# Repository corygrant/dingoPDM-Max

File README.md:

## dingoPDM-Max
dingoPDM-Max is an Infineon Profet based Power Distribution Module. 

# [**Documentation**](https://corygrant.github.io/dingoPDM/)

# [**Store**](https://dingo-electronics.square.site/product/dingopdm-max/9)

## Disclaimer
Please note that this product has been designed by a hobbyist, not a professional. It is intended for off-road and testing use only. Users should operate the product at their own discretion and risk. The designer explicitly disclaims any responsibility for damage or injury that may result from the use of this product.

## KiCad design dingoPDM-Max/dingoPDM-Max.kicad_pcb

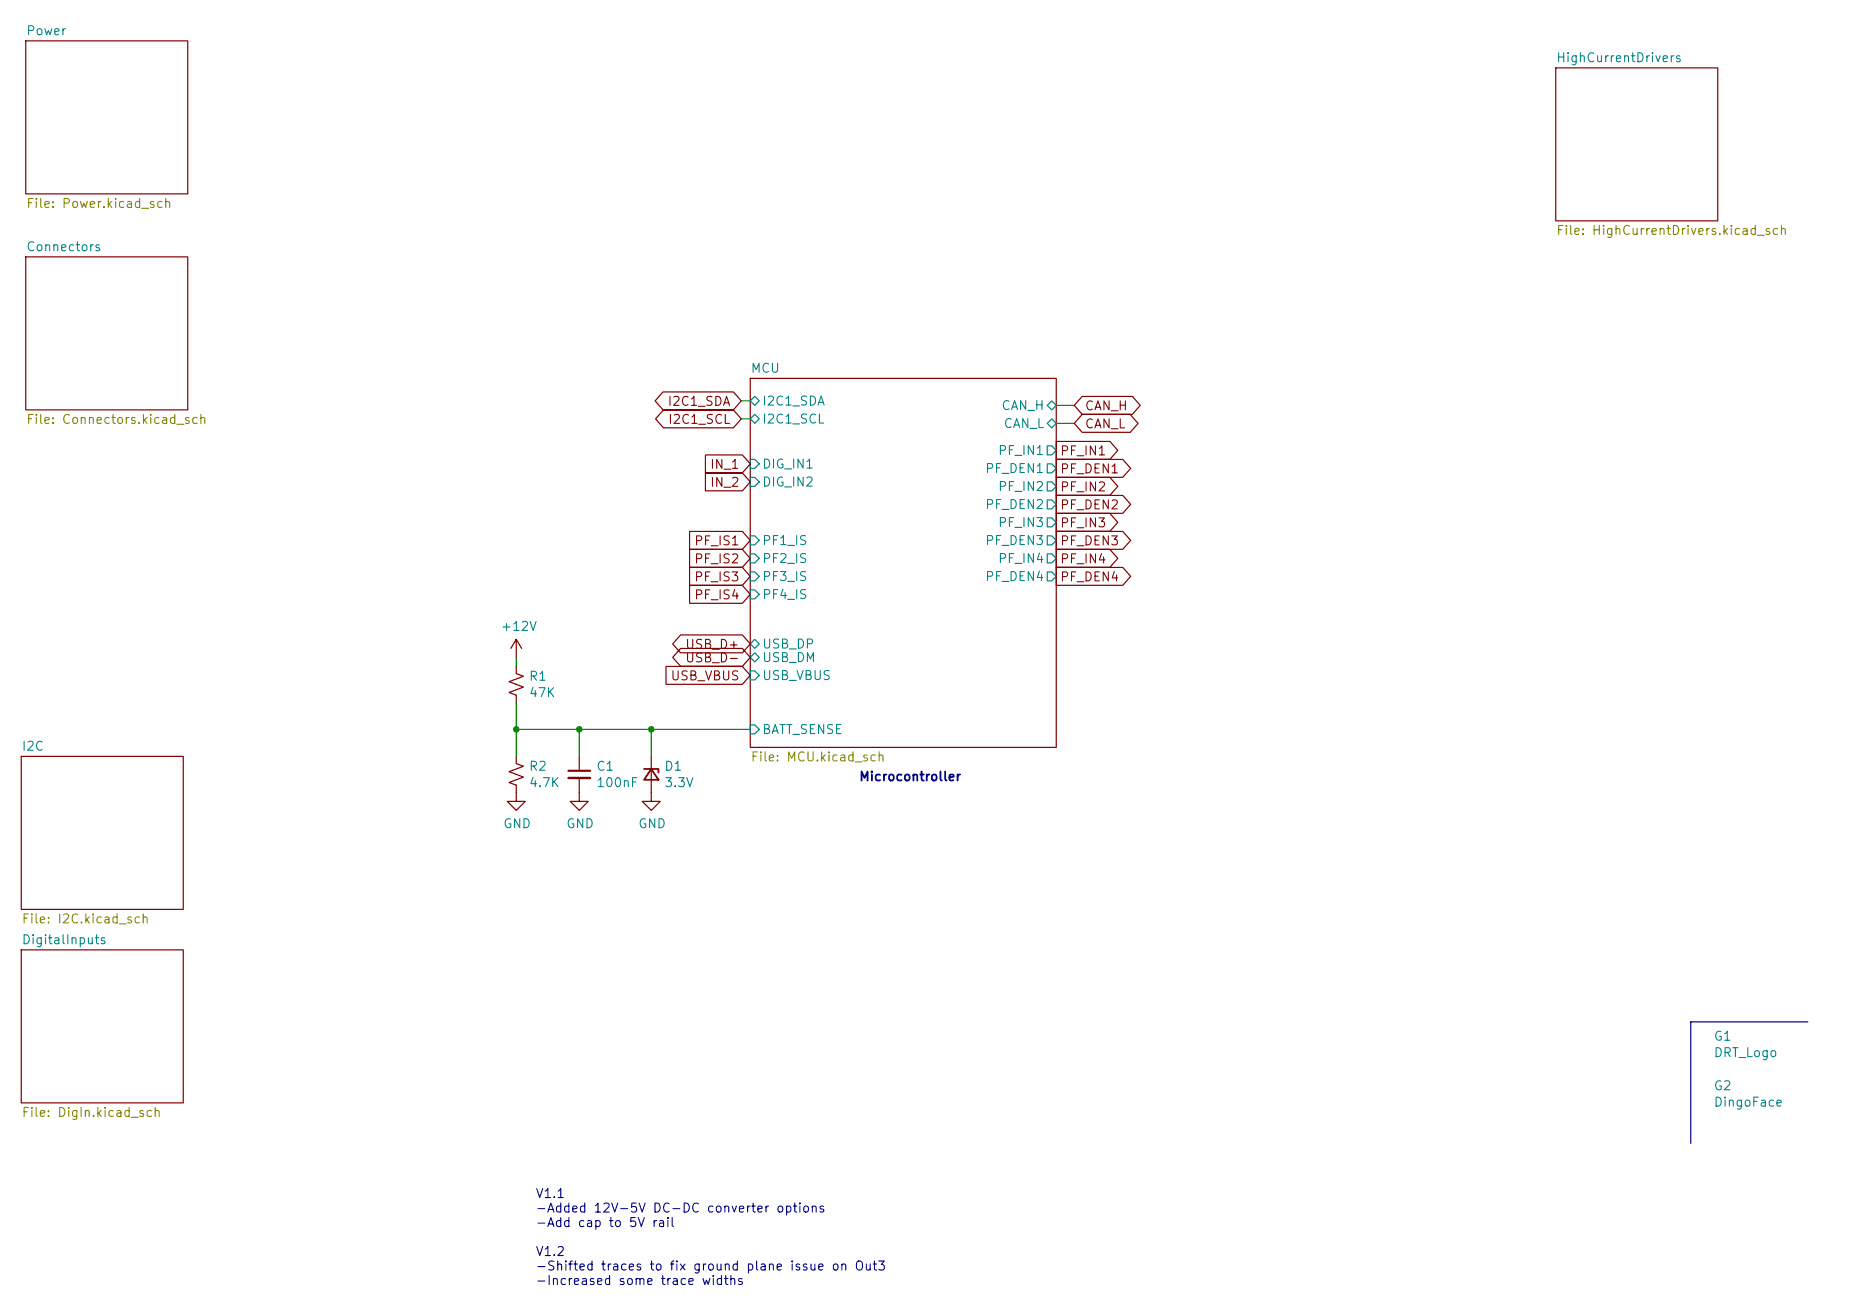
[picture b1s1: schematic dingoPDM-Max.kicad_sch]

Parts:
C1: 100nF; C_0805_2012Metric; Digi-Key_PN 478-1395-1-ND
D1: 3.3V; D_SOD-323_HandSoldering; Digi-Key_PN 1727-5150-1-ND
G1: DRT_Logo; DRTLogo
G2: DingoFace; DingoFaceNoFill
R1: 47K; R_0805_2012Metric; Digi-Key_PN 311-47.0KCRCT-ND
R2: 4.7K; R_0805_2012Metric; Digi-Key_PN 311-4.70KCRCT-ND

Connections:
+12V: R1.1; also elsewhere on the board
/MCU/BATT_SENSE: C1.1, D1.1 (K), R1.2, R2.1; also elsewhere on the board
GND: C1.2, D1.2 (A), R2.2; also elsewhere on the board

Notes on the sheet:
Microcontroller
V1.1 -Added 12V-5V DC-DC converter options -Add cap to 5V rail V1.2 -Shifted traces to fix ground plane issue on Out3 -Increased some trace widths

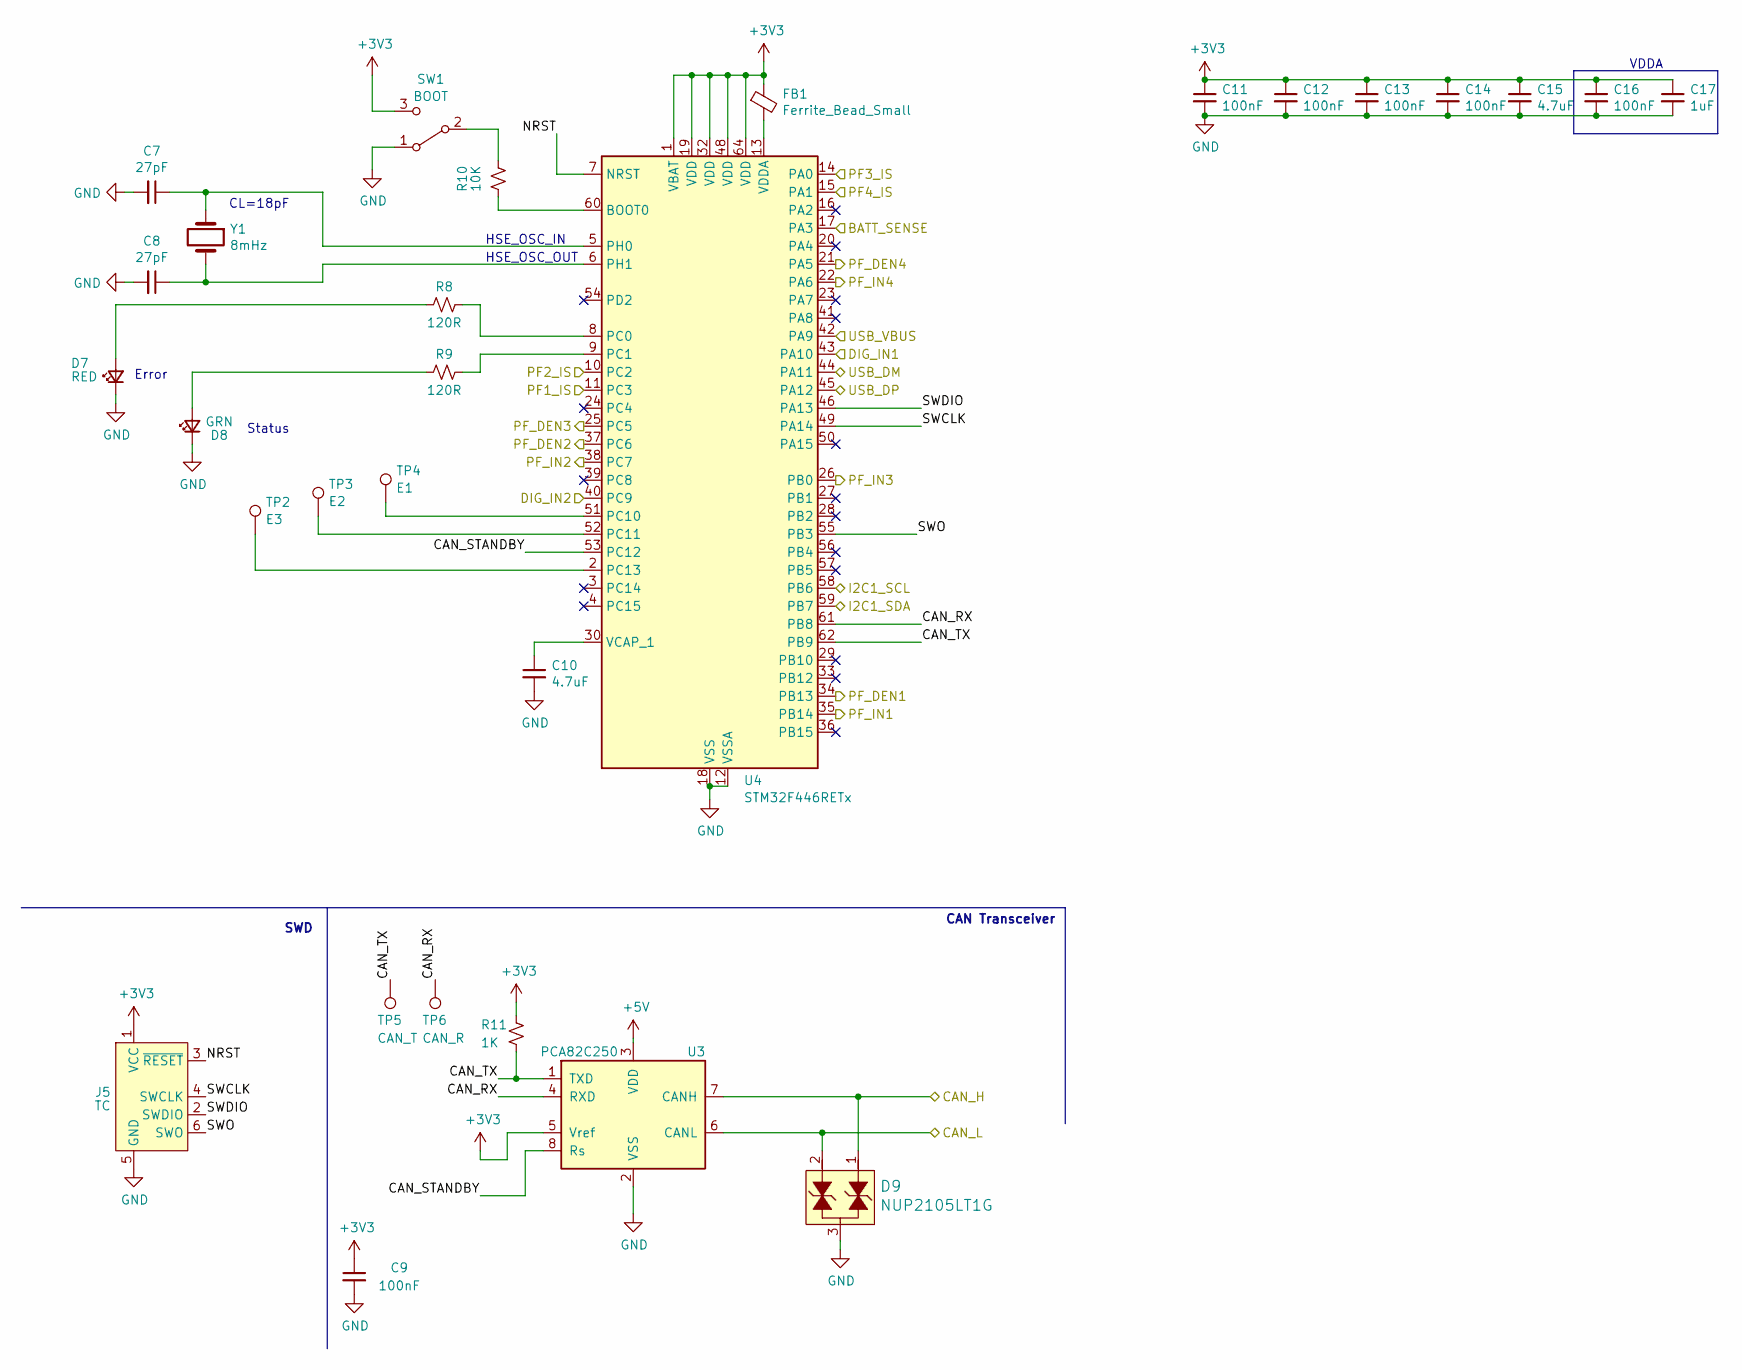
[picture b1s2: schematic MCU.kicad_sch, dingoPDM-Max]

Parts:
C7, C8: 27pF; C_0805_2012Metric; Digi-Key_PN 478-10518-1-ND
C9, C11, C12, C13, C14, C16: 100nF; C_0805_2012Metric; Digi-Key_PN 478-1395-1-ND
C10, C15: 4.7uF; C_0805_2012Metric; Digi-Key_PN 1276-2873-1-ND
C17: 1uF; C_0805_2012Metric; Digi-Key_PN 311-1365-1-ND
D7: RED; LED_0805_2012Metric; Digi-Key_PN 475-1278-1-ND
D8: GRN; LED_0805_2012Metric; Digi-Key_PN 475-1410-1-ND
D9: NUP2105LT1G; SOT-23-3; Digi-Key_PN NUP2105LT1GOSCT-ND
FB1: Ferrite_Bead_Small; R_0805_2012Metric; Digi-Key_PN 490-1054-1-ND
J5: TC; Tag-Connect_TC2030-IDC-NL_2x03_P1.27mm_Vertical
R8, R9: 120R; R_0805_2012Metric; Digi-Key_PN 311-120CRCT-ND
R10: 10K; R_0805_2012Metric; Digi-Key_PN 311-10.0KCRDKR-ND
R11: 1K; R_0805_2012Metric; Digi-Key_PN 311-1.0KARCT-ND
SW1: BOOT; CJS-1200TB; Digi-Key_PN 563-CJS-1200TB1CT-ND
TP2: E3; TestPoint_Keystone_5000-5004_Miniature
TP3: E2; TestPoint_Keystone_5000-5004_Miniature
TP4: E1; TestPoint_Keystone_5000-5004_Miniature
TP5: CAN_T; TestPoint_Keystone_5000-5004_Miniature
TP6: CAN_R; TestPoint_Keystone_5000-5004_Miniature
U3: PCA82C250; SOIC-8_3.9x4.9mm_P1.27mm; Digi-Key_PN 568-10316-1-ND
U4: STM32F446RETx; LQFP-64_10x10mm_P0.5mm; Digi-Key_PN 497-15376-ND
Y1: 8mHz; Crystal_SMD_5032-2Pin_5.0x3.2mm_HandSoldering; Digi-Key_PN 535-10630-1-ND

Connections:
+3V3: C9.1, C11.1, C12.1, C13.1, C14.1, C15.1, C16.1, C17.1, FB1.1, J5.1 (VCC), R11.2, SW1.3 (C), U3.5 (Vref), U4.1 (VBAT), U4.19 (VDD), U4.32 (VDD), U4.48 (VDD), U4.64 (VDD); also elsewhere on the board
+5V: U3.3 (VDD); also elsewhere on the board
/MCU/BATT_SENSE: U4.17 (PA3); also elsewhere on the board
/MCU/CAN_RX: TP6.1, U3.4 (RXD), U4.61 (PB8)
/MCU/CAN_STANDBY: U3.8 (Rs), U4.53 (PC12)
/MCU/CAN_TX: R11.1, TP5.1, U3.1 (TXD), U4.62 (PB9)
/MCU/NRST: J5.3 (~RESET), U4.7 (NRST)
/MCU/SWCLK: J5.4 (SWCLK), U4.49 (PA14)
/MCU/SWDIO: J5.2 (SWDIO), U4.46 (PA13)
/MCU/SWO: J5.6 (SWO), U4.55 (PB3)
CAN_H: D9.1, U3.7 (CANH); also elsewhere on the board
CAN_L: D9.2, U3.6 (CANL); also elsewhere on the board
GND: C7.2, C8.2, C9.2, C10.2, C11.2, C12.2, C13.2, C14.2, C15.2, C16.2, C17.2, D7.1 (K), D8.1 (K), D9.3, J5.5 (GND), SW1.1 (A), U3.2 (VSS), U4.12 (VSSA), U4.18 (VSS), U4.31 (VSS), U4.47 (VSS), U4.63 (VSS); also elsewhere on the board
I2C1_SCL: U4.58 (PB6); also elsewhere on the board
I2C1_SDA: U4.59 (PB7); also elsewhere on the board
IN_1: U4.43 (PA10); also elsewhere on the board
IN_2: U4.40 (PC9); also elsewhere on the board
unnamed: D7.2 (A), R8.2
unnamed: D8.2 (A), R9.2
unnamed: R10.1, SW1.2 (B)
unnamed: R10.2, U4.60 (BOOT0)
unnamed: R8.1, U4.8 (PC0)
unnamed: R9.1, U4.9 (PC1)
unnamed: TP4.1, U4.51 (PC10)
unnamed: TP3.1, U4.52 (PC11)
unnamed: TP2.1, U4.2 (PC13)
unnamed: C7.1, U4.5 (PH0), Y1.1
unnamed: C8.1, U4.6 (PH1), Y1.2
unnamed: C10.1, U4.30 (VCAP_1)
unnamed: FB1.2, U4.13 (VDDA)
PF_DEN1: U4.34 (PB13); also elsewhere on the board
PF_DEN2: U4.37 (PC6); also elsewhere on the board
PF_DEN3: U4.25 (PC5); also elsewhere on the board
PF_DEN4: U4.21 (PA5); also elsewhere on the board
PF_IN1: U4.35 (PB14); also elsewhere on the board
PF_IN2: U4.38 (PC7); also elsewhere on the board
PF_IN3: U4.26 (PB0); also elsewhere on the board
PF_IN4: U4.22 (PA6); also elsewhere on the board
PF_IS1: U4.11 (PC3); also elsewhere on the board
PF_IS2: U4.10 (PC2); also elsewhere on the board
PF_IS3: U4.14 (PA0); also elsewhere on the board
PF_IS4: U4.15 (PA1); also elsewhere on the board
USB_D+: U4.45 (PA12); also elsewhere on the board
USB_D-: U4.44 (PA11); also elsewhere on the board
USB_VBUS: U4.42 (PA9); also elsewhere on the board

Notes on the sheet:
SWD
Error
CAN Transceiver
HSE_OSC_IN
CL=18pF
HSE_OSC_OUT
VDDA
Status

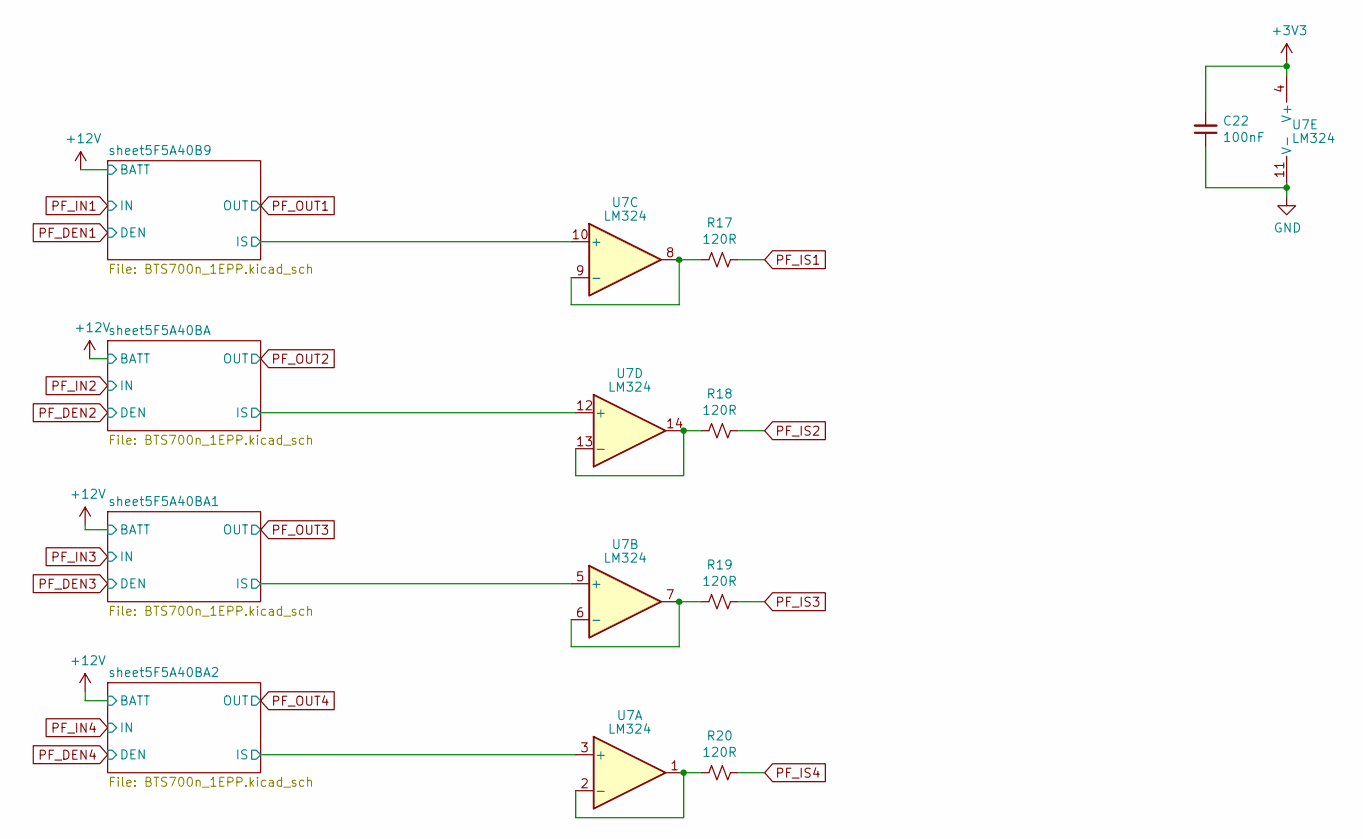
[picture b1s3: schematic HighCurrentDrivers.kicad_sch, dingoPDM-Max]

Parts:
C22: 100nF; C_0805_2012Metric; Digi-Key_PN 478-1395-1-ND
R17, R18, R19, R20: 120R; R_0805_2012Metric; Digi-Key_PN 311-120CRCT-ND
U7: LM324; TSSOP-14_4.4x5mm_P0.65mm; Digi-Key_PN 497-7330-1-ND

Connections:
+3V3: C22.2, U7.4 (V+); also elsewhere on the board
/HighCurrentDrivers/sheet5F5A40B9/IS: U7.10 (+); also elsewhere on the board
/HighCurrentDrivers/sheet5F5A40BA1/IS: U7.5 (+); also elsewhere on the board
/HighCurrentDrivers/sheet5F5A40BA2/IS: U7.3 (+); also elsewhere on the board
/HighCurrentDrivers/sheet5F5A40BA/IS: U7.12 (+); also elsewhere on the board
GND: C22.1, U7.11 (V-); also elsewhere on the board
unnamed: R20.2, U7.1, U7.2 (-)
unnamed: R19.2, U7.6 (-), U7.7
unnamed: R17.2, U7.8, U7.9 (-)
unnamed: R18.2, U7.13 (-), U7.14
PF_IS1: R17.1; also elsewhere on the board
PF_IS2: R18.1; also elsewhere on the board
PF_IS3: R19.1; also elsewhere on the board
PF_IS4: R20.1; also elsewhere on the board

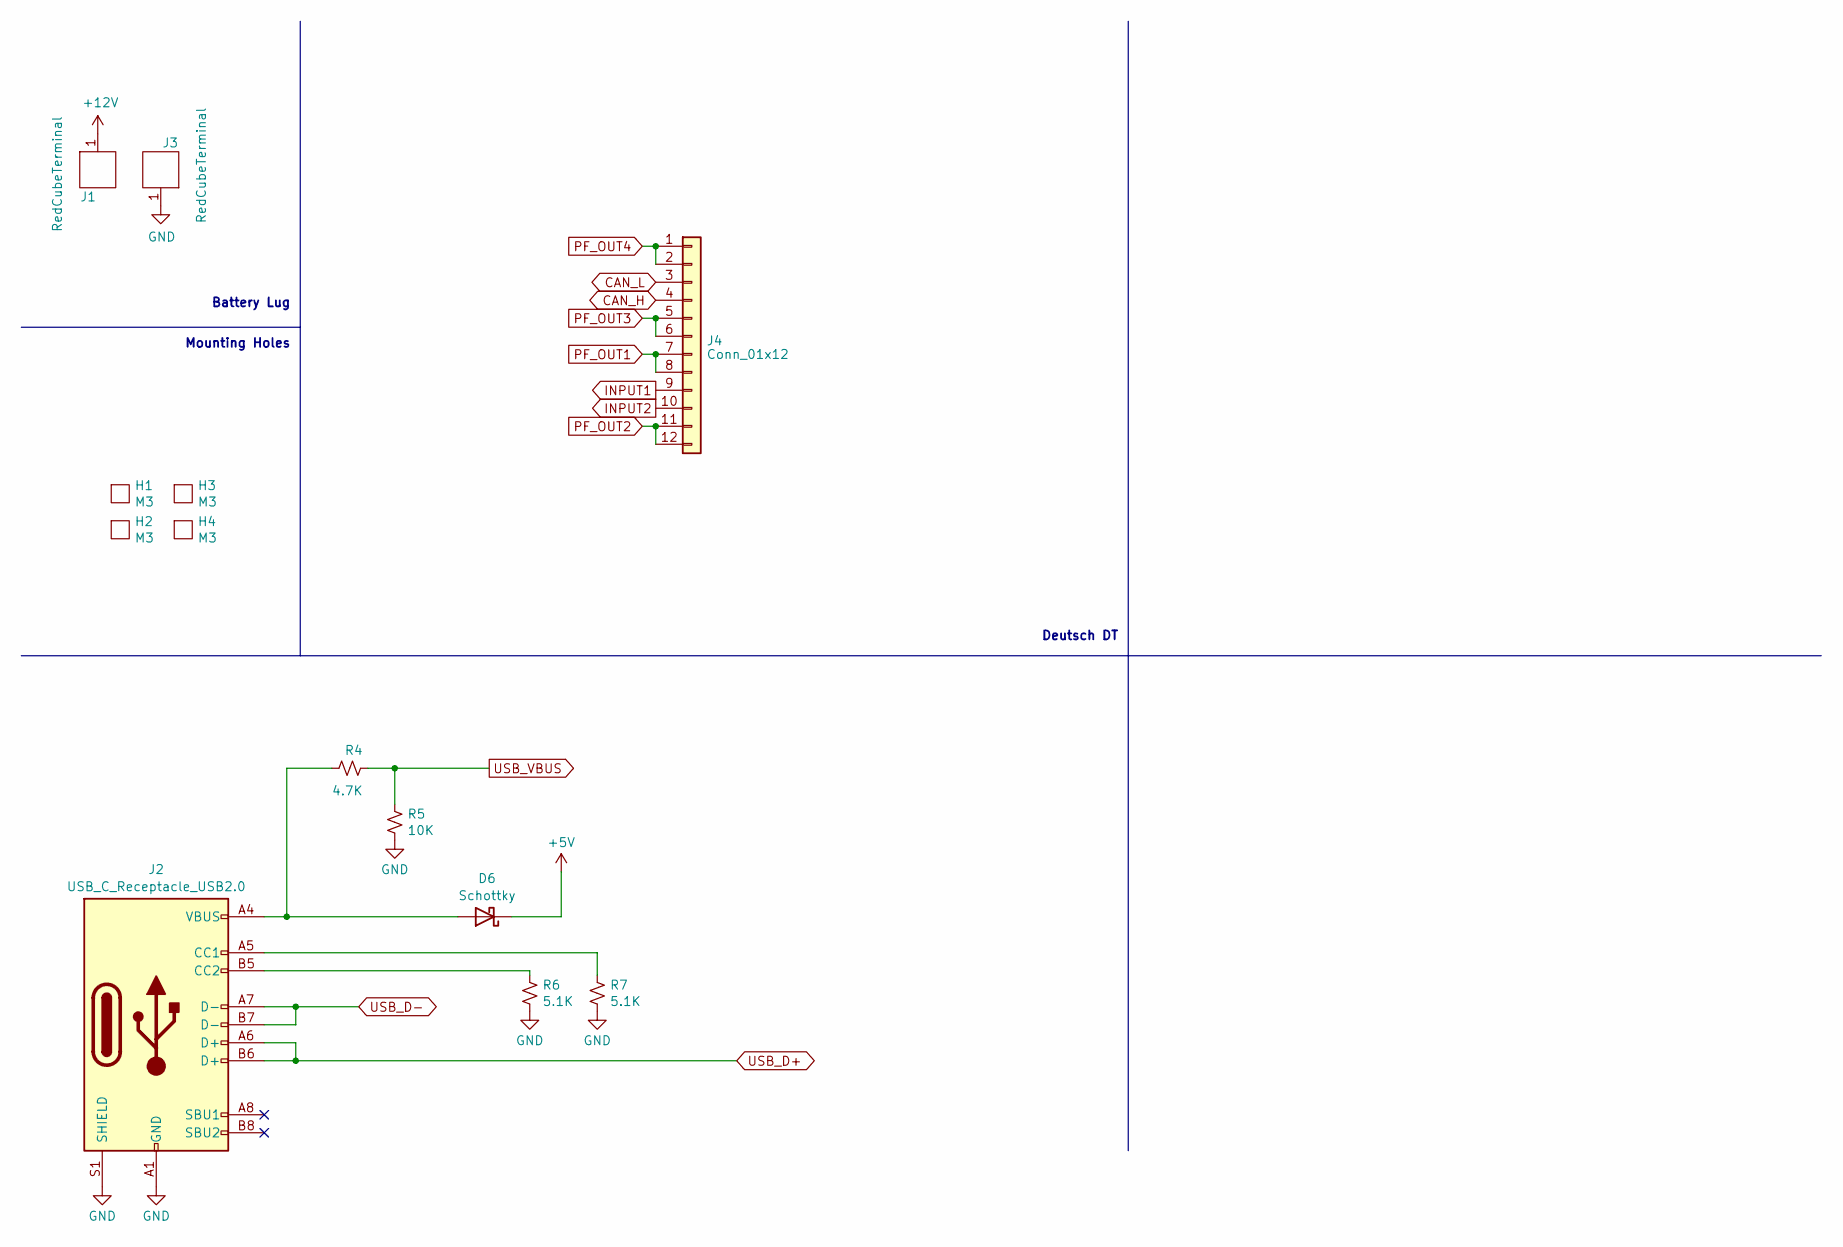
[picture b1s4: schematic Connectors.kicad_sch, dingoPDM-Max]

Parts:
D6: Schottky; D_SOD-123; Digi-Key_PN 1727-2394-1-ND
H1, H2, H3, H4: M3; MountingHole_3.2mm_M3_ISO7380_Pad
J1, J3: RedCubeTerminal; M6_Hole_8Pin_7461084; Digi-Key_PN 732-3203-ND
J2: USB_C_Receptacle_USB2.0; USB_C_Receptacle_GCT_USB4085; Digi-Key_PN 2073-USB4085-GF-ACT-ND
J4: Conn_01x12; DT15-12PA; LCSC C5341788
R4: 4.7K; R_0805_2012Metric; Digi-Key_PN 311-4.70KCRCT-ND
R5: 10K; R_0805_2012Metric; Digi-Key_PN 311-10.0KCRDKR-ND
R6, R7: 5.1K; R_0805_2012Metric; Digi-Key_PN 311-5.1KARCT-ND

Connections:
+5V: D6.1 (K); also elsewhere on the board
+12V: J1.1; also elsewhere on the board
CAN_H: J4.4; also elsewhere on the board
CAN_L: J4.3; also elsewhere on the board
GND: J2.A1 (GND), J2.A12 (GND), J2.B1 (GND), J2.B12 (GND), J2.S1 (SHIELD), J3.1, R5.2, R6.2, R7.2; also elsewhere on the board
INPUT1: J4.9; also elsewhere on the board
INPUT2: J4.10; also elsewhere on the board
unnamed: D6.2 (A), J2.A4 (VBUS), J2.A9 (VBUS), J2.B4 (VBUS), J2.B9 (VBUS), R4.1
unnamed: J2.A5 (CC1), R7.1
unnamed: J2.B5 (CC2), R6.1
PF_OUT1: J4.7, J4.8; also elsewhere on the board
PF_OUT2: J4.11, J4.12; also elsewhere on the board
PF_OUT3: J4.5, J4.6; also elsewhere on the board
PF_OUT4: J4.1, J4.2; also elsewhere on the board
USB_D+: J2.A6 (D+), J2.B6 (D+); also elsewhere on the board
USB_D-: J2.A7 (D-), J2.B7 (D-); also elsewhere on the board
USB_VBUS: R4.2, R5.1; also elsewhere on the board

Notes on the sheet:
Deutsch DT
Battery Lug
Mounting Holes

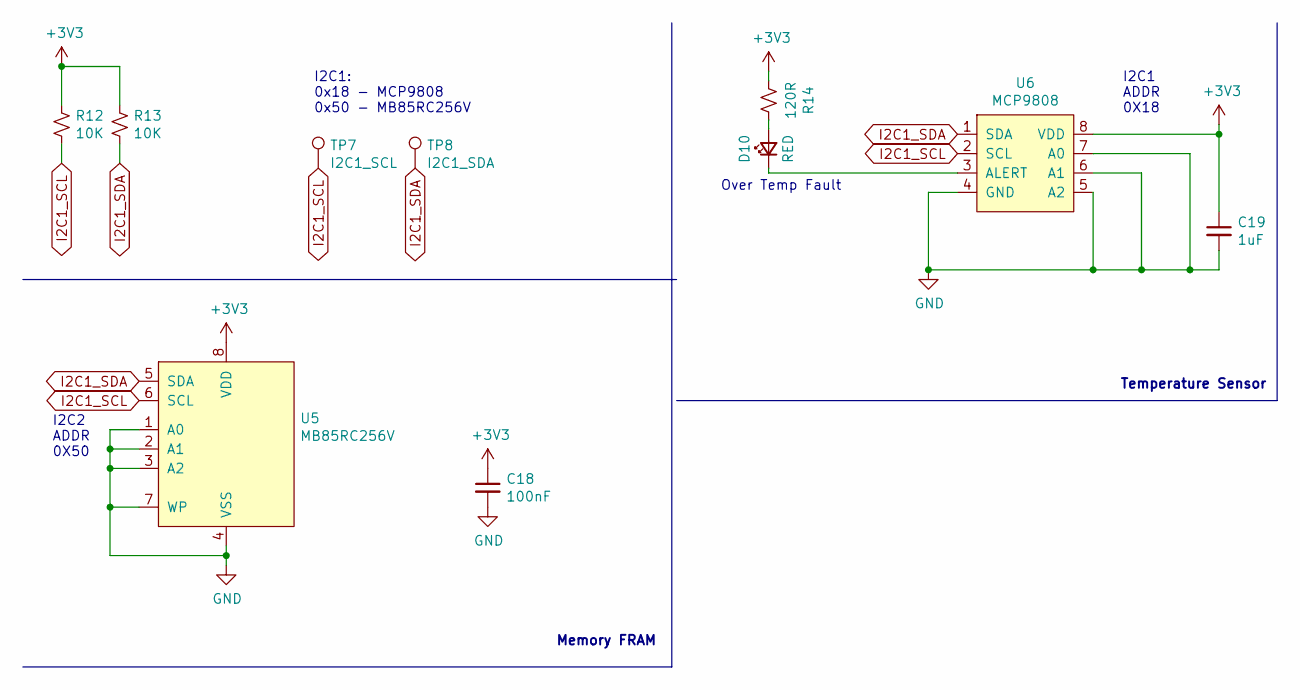
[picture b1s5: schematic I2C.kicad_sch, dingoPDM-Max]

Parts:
C18: 100nF; C_0805_2012Metric; Digi-Key_PN 478-1395-1-ND
C19: 1uF; C_0805_2012Metric; Digi-Key_PN 311-1365-1-ND
D10: RED; LED_0805_2012Metric; Digi-Key_PN 475-1278-1-ND
R12, R13: 10K; R_0805_2012Metric; Digi-Key_PN 311-10.0KCRDKR-ND
R14: 120R; R_0805_2012Metric; Digi-Key_PN 311-120CRCT-ND
TP7: I2C1_SCL; TestPoint_Keystone_5000-5004_Miniature
TP8: I2C1_SDA; TestPoint_Keystone_5000-5004_Miniature
U5: MB85RC256V; SOIC-8_3.9x4.9mm_P1.27mm; Digi-Key_PN 865-1261-1-ND
U6: MCP9808; MSOP-8_3x3mm_P0.65mm; Digi-Key_PN MCP9808T-E/MSCT-ND

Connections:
+3V3: C18.1, C19.1, R12.1, R13.1, R14.2, U5.8 (VDD), U6.8 (VDD); also elsewhere on the board
GND: C18.2, C19.2, U5.1 (A0), U5.2 (A1), U5.3 (A2), U5.4 (VSS), U5.7 (WP), U6.4 (GND), U6.5 (A2), U6.6 (A1), U6.7 (A0); also elsewhere on the board
I2C1_SCL: R12.2, TP7.1, U5.6 (SCL), U6.2 (SCL); also elsewhere on the board
I2C1_SDA: R13.2, TP8.1, U5.5 (SDA), U6.1 (SDA); also elsewhere on the board
unnamed: D10.2 (A), R14.1
unnamed: D10.1 (K), U6.3 (ALERT)

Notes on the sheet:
I2C1 ADDR 0X18
I2C2 ADDR 0X50
Over Temp Fault
Temperature Sensor
I2C1: 0x18 - MCP9808 0x50 - MB85RC256V
Memory FRAM

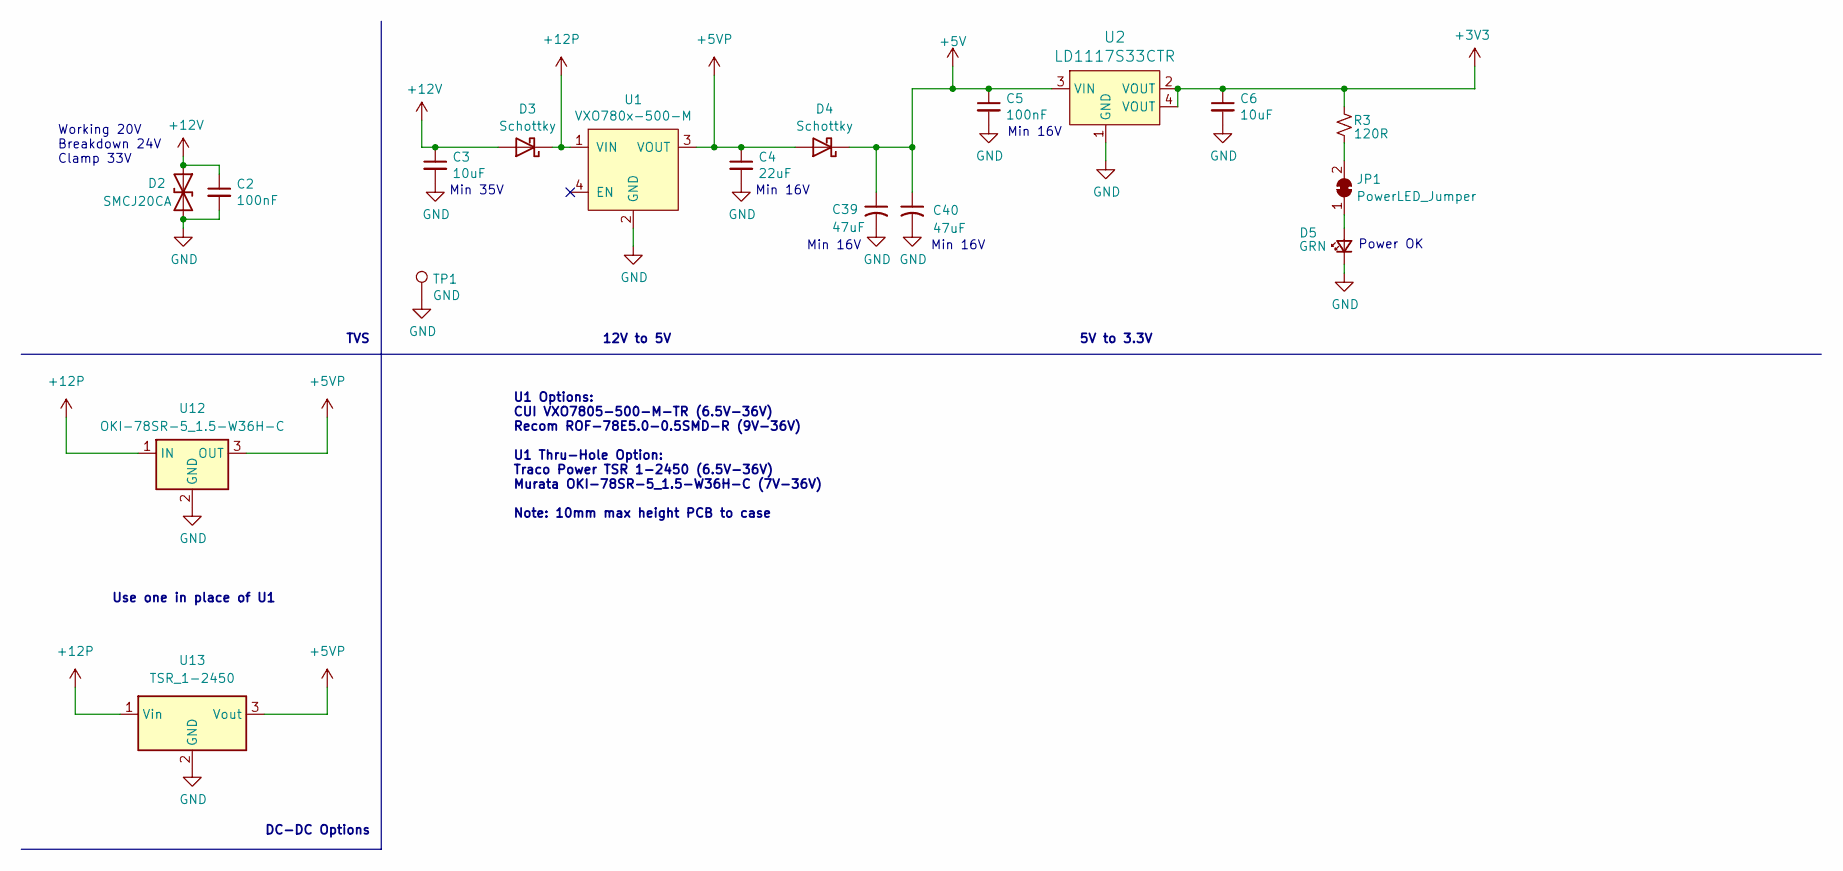
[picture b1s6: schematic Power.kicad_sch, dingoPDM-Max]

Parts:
C2, C5: 100nF; C_0805_2012Metric; Digi-Key_PN 478-1395-1-ND
C3, C6: 10uF; C_0805_2012Metric; Digi-Key_PN 445-11516-1-ND
C4: 22uF; C_0805_2012Metric; Digi-Key_PN 490-10749-1-ND
C39, C40: 47uF; C_2220_5750Metric; Digi-Key_PN 445-7935-1-ND
D2: SMCJ20CA; DO-214AB_TVS; Digi-Key_PN SMCJ20CABCT-ND
D3, D4: Schottky; D_SOD-123; Digi-Key_PN 1727-2394-1-ND
D5: GRN; LED_0805_2012Metric; Digi-Key_PN 475-1410-1-ND
JP1: PowerLED_Jumper; SolderJumper-2_P1.3mm_Bridged_RoundedPad1.0x1.5mm
R3: 120R; R_0805_2012Metric; Digi-Key_PN 311-120CRCT-ND
TP1: GND; TestPoint_Keystone_5000-5004_Miniature
U1: VXO780x-500-M; VXO78x-500-M; Digi-Key_PN 102-VXO7805-500-M-CT-ND
U2: LD1117S33CTR; SOT-223; Digi-Key_PN 497-1241-1-ND
U12: OKI-78SR-5_1.5-W36H-C; Converter_DCDC_Murata_OKI-78SR_Horizontal; Digi-Key_PN 811-2692-ND
U13: TSR_1-2450; Converter_DCDC_TRACO_TSR-1_THT; Digi-Key_PN 1951-2747-ND

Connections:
+3V3: C6.1, R3.2, U2.2 (VOUT), U2.4 (VOUT); also elsewhere on the board
+5V: C5.1, C39.1, C40.1, D4.1 (K), U2.3 (VIN); also elsewhere on the board
+5VP: C4.1, D4.2 (A), U1.3 (VOUT), U12.3 (OUT), U13.3 (Vout)
+12P: D3.1 (K), U1.1 (VIN), U12.1 (IN), U13.1 (Vin)
+12V: C2.1, C3.1, D2.1 (A1), D3.2 (A); also elsewhere on the board
GND: C2.2, C3.2, C4.2, C5.2, C6.2, C39.2, C40.2, D2.2 (A2), D5.1 (K), TP1.1, U1.2 (GND), U2.1 (GND), U12.2 (GND), U13.2 (GND); also elsewhere on the board
unnamed: D5.2 (A), JP1.1 (A)
unnamed: JP1.2 (B), R3.1

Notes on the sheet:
Min 16V
TVS
Min 35V
Power OK
Use one in place of U1
5V to 3.3V
12V to 5V
Working 20V Breakdown 24V Clamp 33V
DC-DC Options
U1 Options: CUI VXO7805-500-M-TR (6.5V-36V) Recom ROF-78E5.0-0.5SMD-R (9V-36V) U1 Thru-Hole Option: Traco Power TSR 1-2450 (6.5V-36V) Murata OKI-78SR-5_1.5-W36H-C (7V-36V) Note: 10mm max height PCB to case

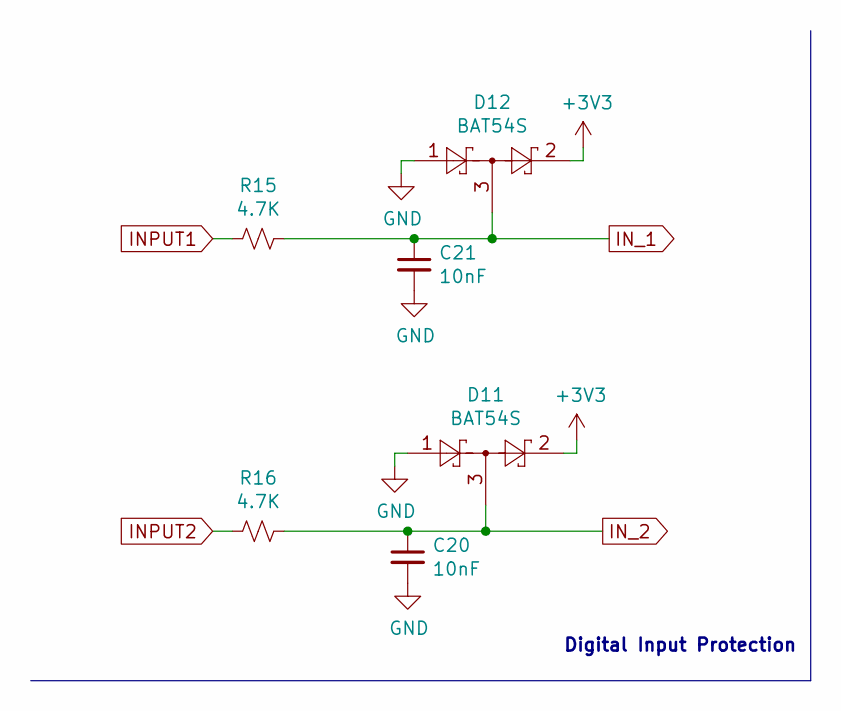
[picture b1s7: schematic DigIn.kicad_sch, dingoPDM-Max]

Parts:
C20, C21: 10nF; C_0805_2012Metric; Digi-Key_PN 311-1136-1-ND
D11, D12: BAT54S; SOT-23; Digi-Key_PN BAT54SLT1GOSCT-ND
R15, R16: 4.7K; R_0805_2012Metric; Digi-Key_PN 311-4.70KCRCT-ND

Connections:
+3V3: D11.2, D12.2; also elsewhere on the board
GND: C20.2, C21.2, D11.1, D12.1; also elsewhere on the board
INPUT1: R15.2; also elsewhere on the board
INPUT2: R16.2; also elsewhere on the board
IN_1: C21.1, D12.3, R15.1; also elsewhere on the board
IN_2: C20.1, D11.3, R16.1; also elsewhere on the board

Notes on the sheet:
Digital Input Protection

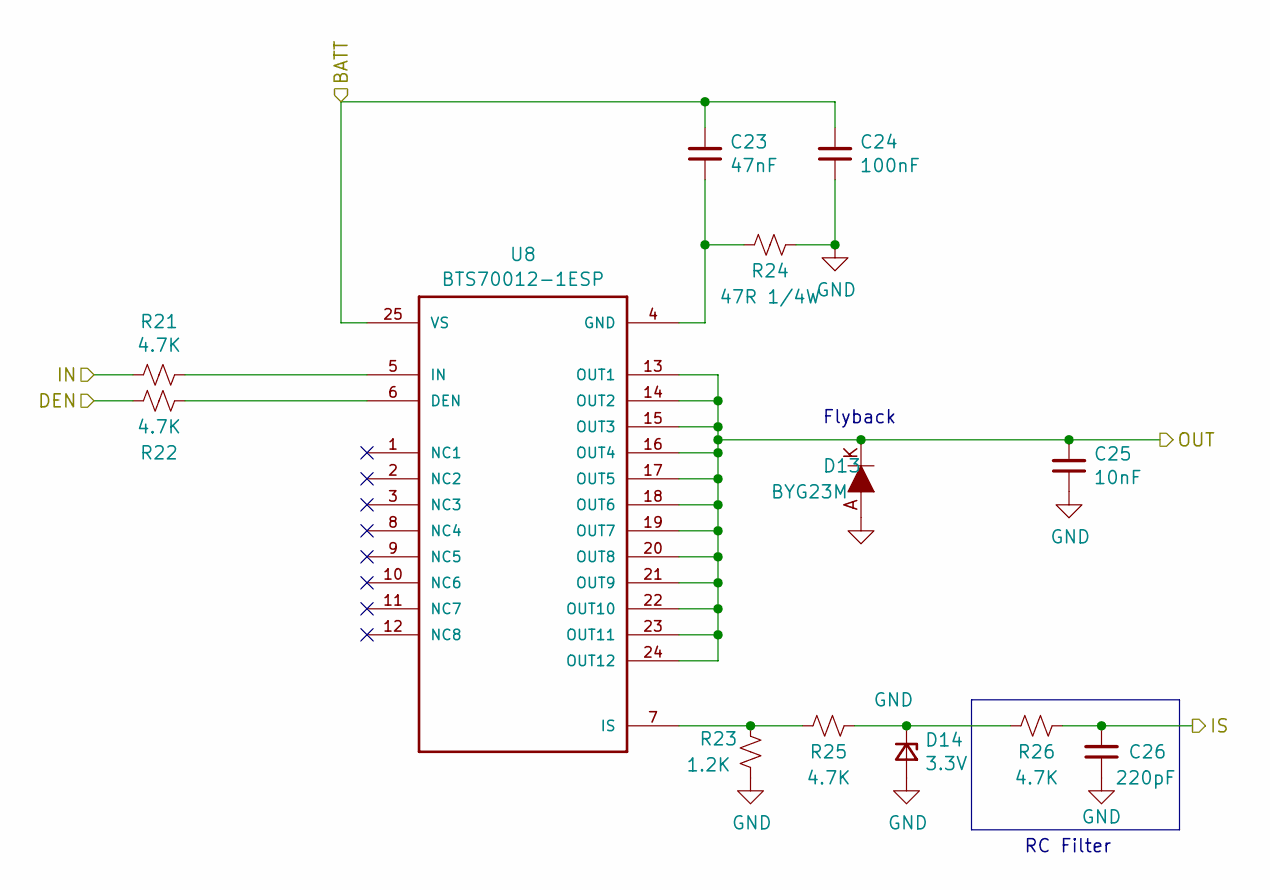
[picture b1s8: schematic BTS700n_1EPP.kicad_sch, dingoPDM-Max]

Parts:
C23: 47nF; C_0805_2012Metric; Digi-Key_PN 399-1166-1-ND
C24: 100nF; C_0805_2012Metric; Digi-Key_PN 478-1395-1-ND
C25: 10nF; C_0805_2012Metric; Digi-Key_PN 311-1136-1-ND
C26: 220pF; C_0805_2012Metric; Digi-Key_PN 399-1138-1-ND
D13: BYG23M; DO-214AC; Digi-Key_PN BYG23M-E3/TR3GICT-ND
D14: 3.3V; D_SOD-323_HandSoldering; Digi-Key_PN 1727-5150-1-ND
R21, R22, R25, R26: 4.7K; R_0805_2012Metric; Digi-Key_PN 311-4.70KCRCT-ND
R23: 1.2K; R_0805_2012Metric; Digi-Key_PN 311-1.20KCRCT-ND
R24: 47R 1/4W; R_1206_3216Metric; Digi-Key_PN 311-47.0FRCT-ND
U8: BTS70012-1ESP; TSDSO-24; Digi-Key_PN 448-BTS700121ESPXUMA2CT-ND

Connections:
+12V: C23.2, C24.2, U8.25 (VS); also elsewhere on the board
/HighCurrentDrivers/sheet5F5A40B9/IS: C26.2, R26.1; also elsewhere on the board
GND: C24.1, C25.1, C26.1, D13.A, D14.2 (A), R23.2, R24.1; also elsewhere on the board
unnamed: D14.1 (K), R25.1, R26.2
unnamed: R22.1, U8.6 (DEN)
unnamed: C23.1, R24.2, U8.4 (GND)
unnamed: R21.1, U8.5 (IN)
unnamed: R23.1, R25.2, U8.7 (IS)
PF_DEN1: R22.2; also elsewhere on the board
PF_IN1: R21.2; also elsewhere on the board
PF_OUT1: C25.2, D13.K, U8.13 (OUT1), U8.14 (OUT2), U8.15 (OUT3), U8.16 (OUT4), U8.17 (OUT5), U8.18 (OUT6), U8.19 (OUT7), U8.20 (OUT8), U8.21 (OUT9), U8.22 (OUT10), U8.23 (OUT11), U8.24 (OUT12); also elsewhere on the board

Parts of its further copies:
C27, C31, C35: 47nF; C_0805_2012Metric; Digi-Key_PN 399-1166-1-ND
C28, C32, C36: 100nF; C_0805_2012Metric; Digi-Key_PN 478-1395-1-ND
C29, C33, C37: 10nF; C_0805_2012Metric; Digi-Key_PN 311-1136-1-ND
C30, C34, C38: 220pF; C_0805_2012Metric; Digi-Key_PN 399-1138-1-ND
D15, D17, D19: BYG23M; DO-214AC; Digi-Key_PN BYG23M-E3/TR3GICT-ND
D16, D18, D20: 3.3V; D_SOD-323_HandSoldering; Digi-Key_PN 1727-5150-1-ND
R27, R28, R31, R32, R33, R34, R37, R38, R39, R40, R43, R44: 4.7K; R_0805_2012Metric; Digi-Key_PN 311-4.70KCRCT-ND
R29, R35, R41: 1.2K; R_0805_2012Metric; Digi-Key_PN 311-1.20KCRCT-ND
R30, R36, R42: 47R 1/4W; R_1206_3216Metric; Digi-Key_PN 311-47.0FRCT-ND
U9, U10, U11: BTS70012-1ESP; TSDSO-24; Digi-Key_PN 448-BTS700121ESPXUMA2CT-ND

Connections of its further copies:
+12V: C27.2, C28.2, C31.2, C32.2, C35.2, C36.2, U9.25 (VS), U10.25 (VS), U11.25 (VS); also elsewhere on the board
/HighCurrentDrivers/sheet5F5A40BA1/IS: C34.2, R38.1; also elsewhere on the board
/HighCurrentDrivers/sheet5F5A40BA2/IS: C38.2, R44.1; also elsewhere on the board
/HighCurrentDrivers/sheet5F5A40BA/IS: C30.2, R32.1; also elsewhere on the board
GND: C28.1, C29.1, C30.1, C32.1, C33.1, C34.1, C36.1, C37.1, C38.1, D15.A, D16.2 (A), D17.A, D18.2 (A), D19.A, D20.2 (A), R29.2, R30.1, R35.2, R36.1, R41.2, R42.1; also elsewhere on the board
unnamed: D16.1 (K), R31.1, R32.2
unnamed: D18.1 (K), R37.1, R38.2
unnamed: D20.1 (K), R43.1, R44.2
unnamed: R28.1, U9.6 (DEN)
unnamed: C27.1, R30.2, U9.4 (GND)
unnamed: R27.1, U9.5 (IN)
unnamed: R29.1, R31.2, U9.7 (IS)
unnamed: R34.1, U10.6 (DEN)
unnamed: C31.1, R36.2, U10.4 (GND)
unnamed: R33.1, U10.5 (IN)
unnamed: R35.1, R37.2, U10.7 (IS)
unnamed: R40.1, U11.6 (DEN)
unnamed: C35.1, R42.2, U11.4 (GND)
unnamed: R39.1, U11.5 (IN)
unnamed: R41.1, R43.2, U11.7 (IS)
PF_DEN2: R28.2; also elsewhere on the board
PF_DEN3: R34.2; also elsewhere on the board
PF_DEN4: R40.2; also elsewhere on the board
PF_IN2: R27.2; also elsewhere on the board
PF_IN3: R33.2; also elsewhere on the board
PF_IN4: R39.2; also elsewhere on the board
PF_OUT2: C29.2, D15.K, U9.13 (OUT1), U9.14 (OUT2), U9.15 (OUT3), U9.16 (OUT4), U9.17 (OUT5), U9.18 (OUT6), U9.19 (OUT7), U9.20 (OUT8), U9.21 (OUT9), U9.22 (OUT10), U9.23 (OUT11), U9.24 (OUT12); also elsewhere on the board
PF_OUT3: C33.2, D17.K, U10.13 (OUT1), U10.14 (OUT2), U10.15 (OUT3), U10.16 (OUT4), U10.17 (OUT5), U10.18 (OUT6), U10.19 (OUT7), U10.20 (OUT8), U10.21 (OUT9), U10.22 (OUT10), U10.23 (OUT11), U10.24 (OUT12); also elsewhere on the board
PF_OUT4: C37.2, D19.K, U11.13 (OUT1), U11.14 (OUT2), U11.15 (OUT3), U11.16 (OUT4), U11.17 (OUT5), U11.18 (OUT6), U11.19 (OUT7), U11.20 (OUT8), U11.21 (OUT9), U11.22 (OUT10), U11.23 (OUT11), U11.24 (OUT12); also elsewhere on the board

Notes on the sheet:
RC Filter
Flyback

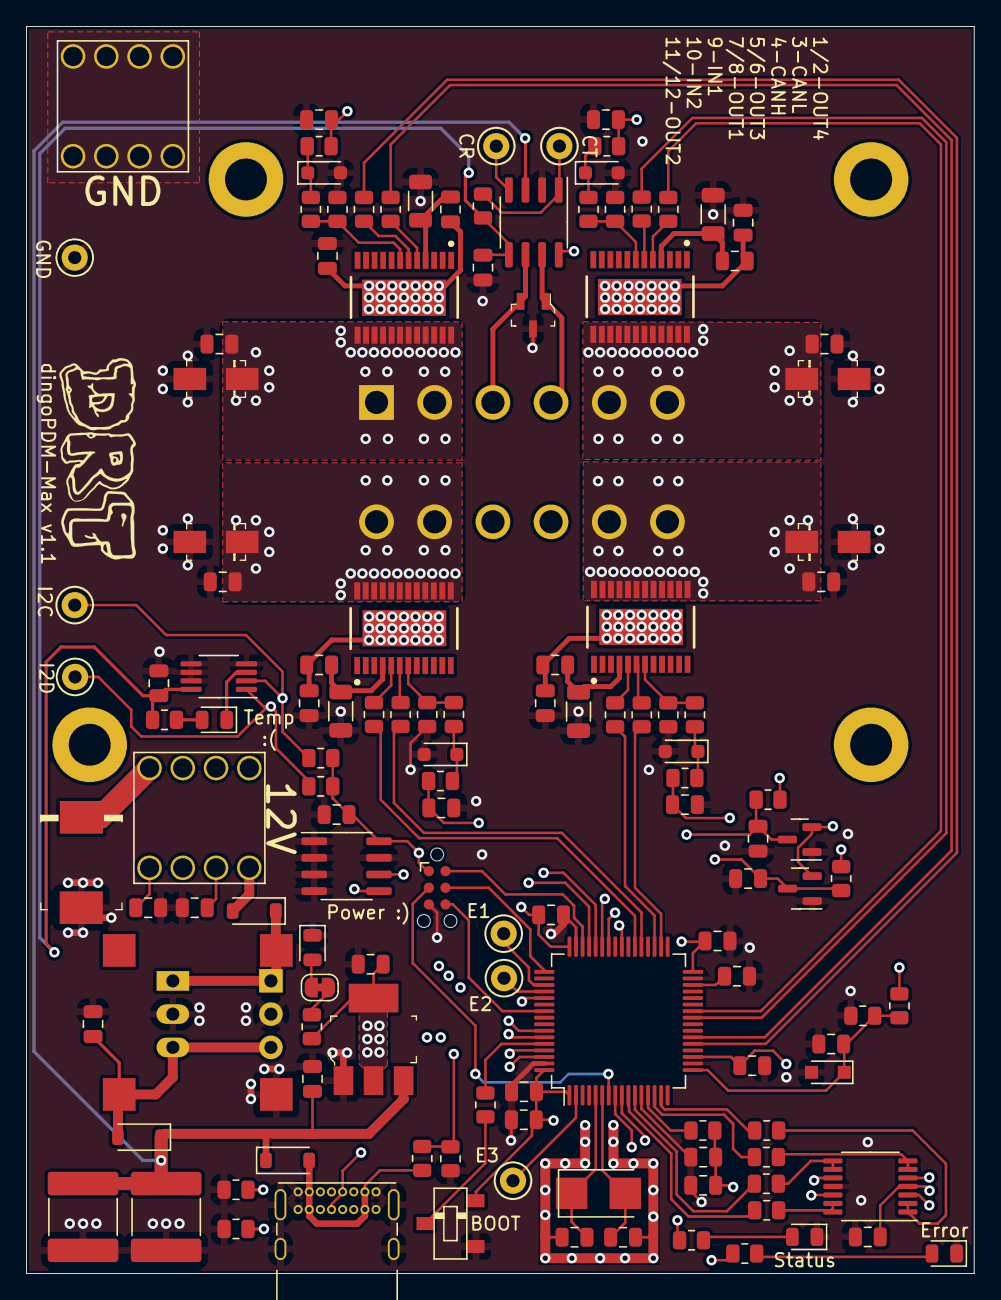
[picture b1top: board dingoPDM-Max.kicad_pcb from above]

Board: 4 copper layers, 72.4 x 95.2 mm, 140 parts (1 on the bottom side), 89 nets.

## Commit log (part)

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2024-07-14 Initial design
2024-07-16 First layout complete
2024-09-06 Updated to Kicad 8
2024-09-06 Another updated Kicad 8 file
2024-09-07 First version ordered
2025-06-17 add dc-dc options and 5v cap
2025-06-17 add exports
2025-06-17 switch to ceramic caps
2025-09-30 fixed bad zone, shifted traces, increase trace widths
    update part numbers for ibom
2025-09-30 add v1.2 export
